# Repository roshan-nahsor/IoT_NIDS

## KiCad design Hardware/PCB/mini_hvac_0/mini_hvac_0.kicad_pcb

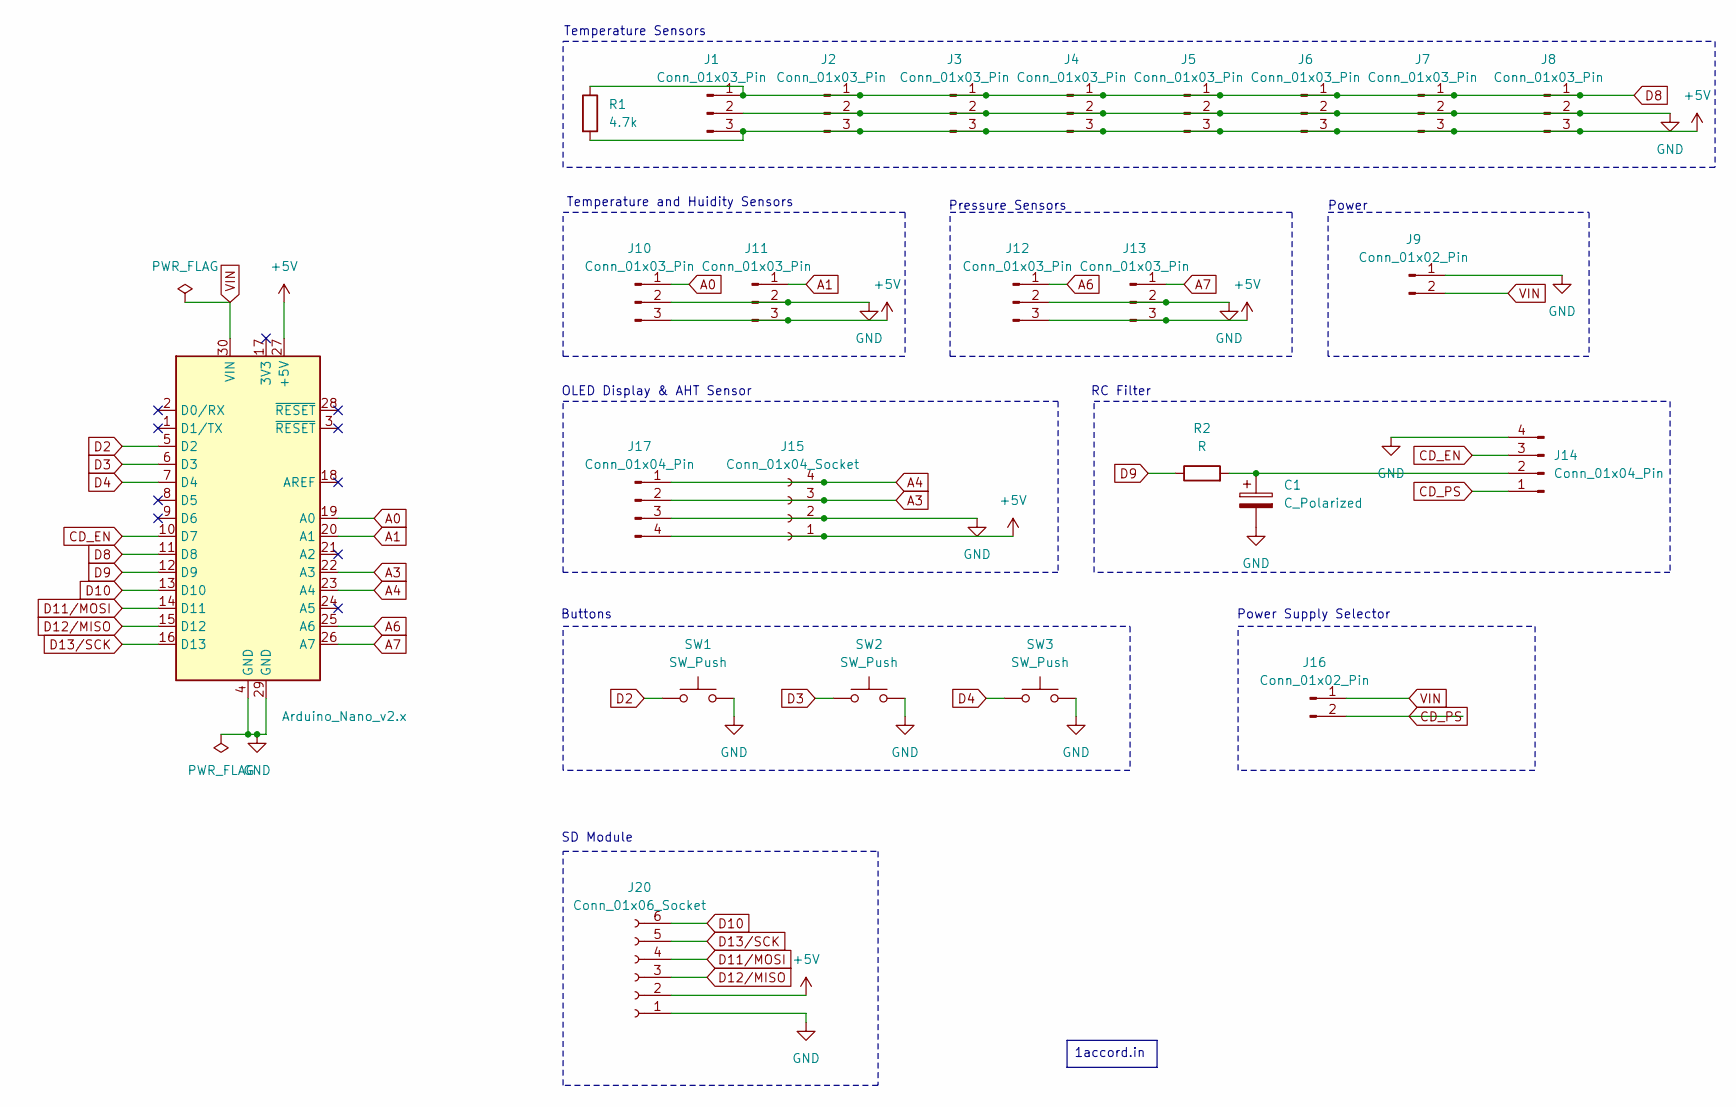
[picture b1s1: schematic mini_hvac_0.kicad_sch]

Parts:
A1: Arduino_Nano_v2.x; Arduino_Nano
C1: C_Polarized; CP_Radial_D5.0mm_P2.00mm
J1, J2, J3, J4, J5, J6, J7, J8, J10, J11, J12, J13: Conn_01x03_Pin; JST_XH_B3B-XH-A_1x03_P2.50mm_Vertical
J9: Conn_01x02_Pin; JST_XH_B2B-XH-A_1x02_P2.50mm_Vertical
J14, J17: Conn_01x04_Pin; JST_XH_B4B-XH-A_1x04_P2.50mm_Vertical
J15: Conn_01x04_Socket; PinSocket_1x04_P2.54mm_Vertical
J16: Conn_01x02_Pin; PinHeader_1x02_P2.00mm_Vertical
J20: Conn_01x06_Socket; PinSocket_1x06_P2.54mm_Vertical
R1: 4.7k; R_Axial_DIN0207_L6.3mm_D2.5mm_P7.62mm_Horizontal
R2: R; R_Axial_DIN0207_L6.3mm_D2.5mm_P7.62mm_Horizontal
SW1, SW2, SW3: SW_Push; SW_PUSH_6mm_H7.3mm

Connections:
+5V: A1.27 (+5V), J1.3, J2.3, J3.3, J4.3, J5.3, J6.3, J7.3, J8.3, J10.3, J11.3, J12.3, J13.3, J15.1, J17.4, J20.2, R1.2
A0: A1.19 (A0), J10.1
A1: A1.20 (A1), J11.1
A3: A1.22 (A3), J15.3, J17.2
A4: A1.23 (A4), J15.4, J17.1
A6: A1.25 (A6), J12.1
A7: A1.26 (A7), J13.1
CD_EN: A1.10 (D7), J14.3
CD_PS: J14.1, J16.2
D2: A1.5 (D2), SW1.1
D3: A1.6 (D3), SW2.1
D4: A1.7 (D4), SW3.1
D8: A1.11 (D8), J1.1, J2.1, J3.1, J4.1, J5.1, J6.1, J7.1, J8.1, R1.1
D9: A1.12 (D9), R2.1
D10: A1.13 (D10), J20.6
D11/MOSI: A1.14 (D11), J20.4
D12/MISO: A1.15 (D12), J20.3
D13/SCK: A1.16 (D13), J20.5
GND: A1.4 (GND), A1.29 (GND), C1.2, J1.2, J2.2, J3.2, J4.2, J5.2, J6.2, J7.2, J8.2, J9.1, J10.2, J11.2, J12.2, J13.2, J14.4, J15.2, J17.3, J20.1, SW1.2, SW2.2, SW3.2
unnamed: C1.1, J14.2, R2.2
VIN: A1.30 (VIN), J9.2, J16.1

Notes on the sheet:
Temperature and Huidity Sensors
Pressure Sensors
Buttons
SD Module
Power Supply Selector
RC Filter
OLED Display & AHT Sensor
Temperature Sensors
Power
1accord.in

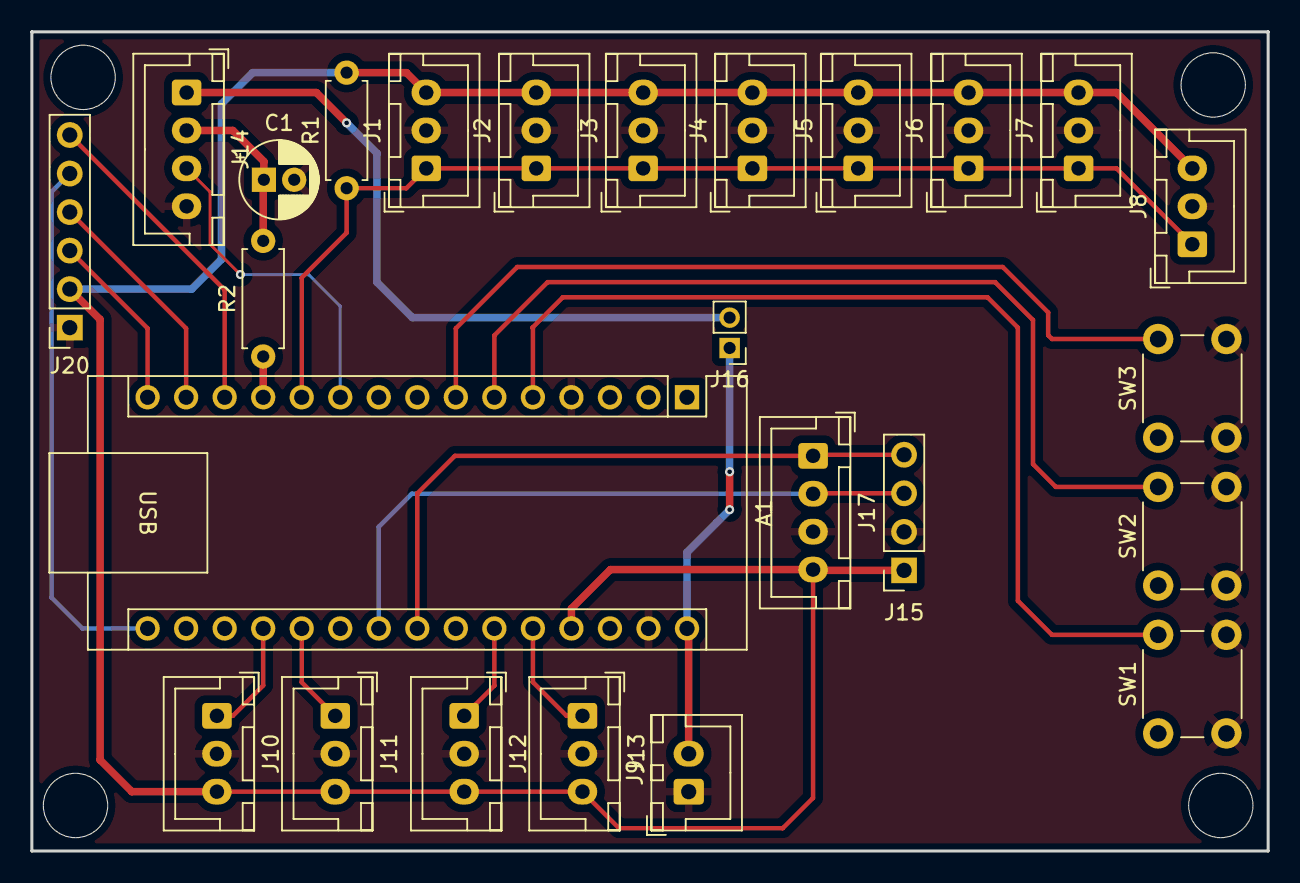
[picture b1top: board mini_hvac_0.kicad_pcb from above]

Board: 2 copper layers, 81.5 x 54.0 mm, 25 parts (0 on the bottom side), 21 nets.

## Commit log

2024-11-06 good code
2024-11-14 PyShark configured to print traffic
2024-11-14 csv added
2024-11-14 pyshark to csv
2025-04-23 New Capture code to view tcp and mqtt header receiving packets when esp connected/d&disconnected
2025-04-23 trained model
2025-04-24 capture script and traffic pcap
2025-04-26 pickle files
2025-04-26 model saving files
2025-04-26 Requirements
2025-04-26 saturday csv and python code
2025-04-27 csv script
2025-04-27 home automation system
    Ultrasonic + Temperature Sensor
2025-05-02 dataset with attack
2025-05-02 Create delete
2025-05-03 presentation
2025-05-03 presentation new
2025-05-06 final code files
2025-05-06 final cnn code files
2025-05-24 Datasheets and Diagram added
2025-05-24 test setup 2 diagram
2025-05-24 document links added
2025-05-25 nano module based PCB added
2025-05-28 KiCad generated BoM
2025-05-29 mechanical files added
2025-05-30 added AHT header and power selector
2025-05-30 changed PS from net label to global label
2025-05-30 routed power selector and generated BoM
2025-06-02 fan datasheet added
2025-06-02 feat: add enable/disable compressor
2025-06-02 footprint changes and schematic clean up
2025-06-02 new PCB layout
2025-06-02 even smaller layout, horizontal footprints replaced with vertical and orientation changed
2025-06-02 no change, change undone
2025-06-02 final pcb, shrinked
2025-06-02 final pcb, recommit
2025-06-03 gerber files
2025-06-03 atmega328p datasheet and gerbers (but why?)
2025-06-03 updated gerber
2025-06-06 chore: edit eol=lf
2025-06-06 test_steup_4.0 (same as log_test.ino)
2025-06-06 u8g2 replaced with u8x8
2025-06-06 feat: data is logging
2025-06-06 perf: replaced drawString() with setCursor()+print()
2025-06-08 working u8x8
2025-06-08 basic working
2025-06-08 refactor: functionalised sd
2025-06-08 moved to sd.cpp
2025-06-08 functionalised and moved to display.cpp
2025-06-08 buttons.cpp created
2025-06-09 feat: buttons working
2025-06-09 feat: step displaying
2025-06-09 feat: ds tested if RF sensor and displayed
2025-06-09 feat: save on button press
2025-06-09 feat: dht sensor integrated and displayed
2025-06-09 feat: added all values to display
2025-06-09 small change to button
2025-06-11 fix: shifted c to left
2025-06-16 feat: added save indicator LED
2025-06-17 fix: init for LED
2025-06-17 feat: different debounce logic
2025-06-17 feat: use save button as function button to toggle compressor
2025-06-17 feat: save button shifted to FUNC+UP
2025-06-17 commented speed and step printing on serial monitor
2025-06-17 all features added
2025-06-17 commented serial print statements
2025-06-18 feat: software controlled compressor enable/disable
2025-06-18 fix: working logic using bitwise operation
2025-06-18 fix: initialised to be off
2025-06-18 chore: removed debug statements
2025-06-18 fix: update analogwrite when EN toggled chore: commented init statements
2025-06-18 display pressure
2025-06-19 fix: change ISR mode for button interrupts to LOW
    Before this the interrupts were triggering randomly; noticed while resetting the microcontroller
2025-06-19 fix: new log file with headers printing in log
2025-06-19 perf: placed the header string in F macro
    Before this the saved values on the SD card were corrupted
2025-06-20 fix: new CI id replaced
2025-06-23 feat: all variables displaying and saving on sd without corruption
    fix: corrected csv syntax
2025-06-24 feat: added compressor temperature threshold
2025-06-24 feat: display warning
2025-06-24 fix: conditional display warning
2025-06-24 fix: compressor file added
